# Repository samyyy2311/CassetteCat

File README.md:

# CassetteCat

<p align="center">
  <strong>A privacy-first Android music player for local media ownership and self-hosted streaming.</strong>
</p>

<p align="center">
  Desktop app: <a href="https://github.com/samyyy2311/CassetteCat-Desktop">CassetteCat Desktop</a> (Windows, macOS, Linux)
</p>

<p align="center">
  Website: <a href="https://cassettecat.caffeinelabs.in">cassettecat.caffeinelabs.in</a> · User guide: <a href="https://cassettecat.caffeinelabs.in/docs">cassettecat.caffeinelabs.in/docs</a>
</p>

<p align="center">

  <br />

</p>

---

## Install

<table align="center">
  <tr>
    <td align="center"></td>
    <td align="center"></td>
    <td align="center"></td>
    <td align="center"></td>
    <td align="center"></td>
  </tr>
</table>

<p align="center">
  <strong>Android 8.0+</strong><br />
  Download the latest APK directly from GitHub or use Obtainium for automatic update tracking. F-Droid and OpenAPK listings are pending.
</p>

---

## Screenshots

---

## Features

### Audio & Playback

- **Media3 Playback Engine**: Background audio playback with lock screen
  controls, system media notifications, and state restoration on launch.
- **Hardware Equalizer & DSP**: 5-band graphic EQ, bass boost, virtualizer, and
  loudness enhancer. Includes calibrated headphone presets powered by
  [AutoEq](https://github.com/jaakkopasanen/AutoEq).
- **Volume Normalization (ReplayGain)**: Automatic track volume balancing to
  avoid sudden loudness spikes.
- **Volume Limit (Ear Protection)**: Optional hard cap on maximum output level,
  independent of system volume.
- **Synchronized Lyrics**: Real-time karaoke-style lyrics via
  [LRCLIB](https://lrclib.net), embedded ID3 tags, and local `.lrc` sidecars
  with configurable typography scaling and keep-screen-awake mode.
- **Sleep Timer & Smart Disconnect**: Sleep timer to pause playback, plus
  instant pause when headphones or Bluetooth disconnect.

### Library & Streaming

- **Local Audio Scanning**: Scans device audio with configurable folder
  whitelists, blacklists, and short audio clip filtering.
- **A–Z Rail**: Jump through long lists with a letter badge and a light tick as
  you pass each letter.
- **Search**: Finds songs, artists, and albums as you type, matching several
  words at once.
- **Subsonic API**: Connects to Navidrome, Gonic, and Airsonic with token
  authentication.
- **Jellyfin**: Direct streaming and music library browsing from your Jellyfin
  server, with Quick Connect sign-in support.
- **Internet Radio**: Search and browse tens of thousands of live stations from
  [Radio Browser](https://www.radio-browser.info) by name, tag, or country, with
  favorites and Android Auto support.
- **Offline Cache**: Download and cache streaming tracks for offline playback.
- **Scrobbling**: Track your listening on [Last.fm](https://www.last.fm),
  [ListenBrainz](https://listenbrainz.org), and [Libre.fm](https://libre.fm).
- **Listening Record**: Your top songs, artists, and albums by month or year,
  your listening history, and a Rewind poster to share.
- **Listening Room**: Sync playback with nearby devices over your local Wi-Fi.

### Planned Companion Hardware

> The companion protocol is present in the Android app, but the `firmware/` and
> `hardware/` directories currently contain design placeholders rather than
> buildable firmware or fabrication files.

- **Wireless Pairing**: Connect to a standalone ESP32 CassetteCat player over a
  direct SoftAP hotspot or your local Wi-Fi network via mDNS. On Android 13+,
  hotspot pairing associates automatically via `WifiNetworkSpecifier`.
- **Live Telemetry**: Battery level, charging status, SD card capacity, and
  firmware version, all from the Pairing screen.

### Device Integration

- **Android Auto**: Browse your local library (Liked Songs, Playlists, Albums,
  Artists, All Songs) and radio favourites, search, and control playback from
  the car.
- **Quick Settings Tile**: Play, pause, and see what's playing without opening
  the app.
- **Desktop Remote**: Pick your computer from the devices button to control
  [CassetteCat Desktop](https://github.com/samyyy2311/CassetteCat-Desktop) on
  the same Wi-Fi, move your song, queue and position between the two, and
  browse the computer's music from your phone.

### Design & Customization

- **Curated Theme Accents**: 6 dynamic color palettes: _Record Red_, _Cassette
  Amber_, _Electric Cyan_, _Neon Emerald_, _Tape Magenta_, and _Monochrome
  Silver_.
- **Pure Black AMOLED Mode**: Pitch black `#000000` surface backgrounds for true
  OLED blacks and maximum battery efficiency.
- **Now Playing & Artwork Styling**: Configurable album art corner radii (Curved
  16dp, Soft 8dp, Vinyl Square 0dp) and interactive remaining time countdown
  toggle (`-02:45`).
- **Navigation & Startup Preferences**: Configurable default landing screen
  (_Home_, _Library_, or _Last active tab_) and default Library section.
- **Share Cards**: Share a song or a few lines of its lyrics as a 2160×2700
  image.
- **Home Screen Widget**: Resizable, with the current song and artwork, play
  controls, shuffle, repeat, and like, in your accent colour. Play works even
  after the app is closed.

### Privacy

- Local-first architecture: no analytics, no third-party tracking, zero Google
  Play Services dependencies.
- Streaming server credentials encrypted with AES-256 via the hardware-backed
  `AndroidKeyStore`.
- Fully open source under GPL-3.0.
- F-Droid submission pending.

---

## Building

```bash
cd app
./gradlew assembleDebug
./gradlew testDebugUnitTest
```

Output:

```text
app/app/build/outputs/apk/debug/app-debug.apk
```

---

## Documentation

- [User guide](https://cassettecat.caffeinelabs.in/docs): setup, every feature, and troubleshooting
- [Developer guide](docs/README.md#working-on-the-code): building, architecture, how-tos and releasing
- [Privacy Policy](PRIVACY_POLICY.md)
- [Third-Party Notices](THIRD_PARTY_NOTICES.md)

---

## Contributing

Bug reports, ideas and pull requests are welcome. Read [CONTRIBUTING.md](CONTRIBUTING.md) before opening a pull
request, and [AI_DISCLOSURE.md](AI_DISCLOSURE.md) for how AI assistance is used here.

### Translations

Translate the app in your browser on Weblate, with no coding needed. Weblate sends your work here as a pull request,
and anything not translated yet shows in English. See [TRANSLATING.md](TRANSLATING.md) for a few guidelines. The
desktop app is English only for now ([CassetteCat-Desktop#56](https://github.com/samyyy2311/CassetteCat-Desktop/issues/56)).

---

## Support

CassetteCat is free, with no ads and no tracking. If it's useful to you, you can support its development:

---

## Credits

### Services & Data

| Project | Used for |
| :--- | :--- |
| [LRCLIB](https://lrclib.net) | Synchronized and plain lyrics |
| [Cover Art Archive](https://coverartarchive.org) | Album artwork from MetaBrainz and the Internet Archive |
| [MusicBrainz](https://musicbrainz.org) | Music metadata and encyclopedia |
| [Last.fm](https://www.last.fm) | Scrobbling |
| [ListenBrainz](https://listenbrainz.org) | Open scrobbling |
| [Radio Browser](https://www.radio-browser.info) | Internet radio station directory |
| [Libre.fm](https://libre.fm) | Free software scrobbling (GNU FM) |
| [Wikipedia](https://wikipedia.org) | Artist biographies (CC BY-SA 4.0) |
| [Deezer](https://deezer.com) and [TheAudioDB](https://theaudiodb.com) | Artist imagery and metadata |
| [GitHub](https://github.com) | Release update checks |

### Libraries & Design

| Project | Used for |
| :--- | :--- |
| [AutoEq](https://github.com/jaakkopasanen/AutoEq) | Headphone EQ profiles by Jaakko Pasanen |
| [AndroidX Media3](https://developer.android.com/media/media3) | Playback engine and caching |
| [Jetpack Compose](https://developer.android.com/jetpack/compose) | UI toolkit |
| [Lucide](https://lucide.dev) | App logo and icons (ISC) |
| [Simple Icons](https://simpleicons.org) | Brand icons (CC0 1.0) |
| [OkHttp](https://github.com/square/okhttp) | HTTP client |
| [IBM Plex](https://github.com/IBM/plex) | Typefaces (OFL 1.1) |
| [Space Grotesk](https://github.com/floriankarsten/space-grotesk) | Display font by Florian Karsten (OFL 1.1) |

---

## Desktop

CassetteCat is also available for Windows, macOS, and Linux at
[CassetteCat-Desktop](https://github.com/samyyy2311/CassetteCat-Desktop).

---

## Acknowledgements

<p align="center">

</p>

<p align="center">
  Thanks to <a href="https://coderabbit.ai">CodeRabbit</a> for free code reviews on open-source projects like this one, to <a href="https://hosted.weblate.org/engage/cassettecat/">Weblate</a> for hosting translations, and to <a href="https://www.codacy.com">Codacy</a>, <a href="https://www.codefactor.io">CodeFactor</a> and <a href="https://www.mintlify.com">Mintlify</a> for their free plans for open source.
</p>

---

## License

CassetteCat is licensed under the
[GNU General Public License v3.0 (GPL-3.0)](LICENSE).

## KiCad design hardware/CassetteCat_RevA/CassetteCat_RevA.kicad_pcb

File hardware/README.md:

# CassetteCat Hardware

PCB schematics, board layouts, and mechanical design files for the CassetteCat player. Licensed under [CERN-OHL-S-2.0](LICENSE).

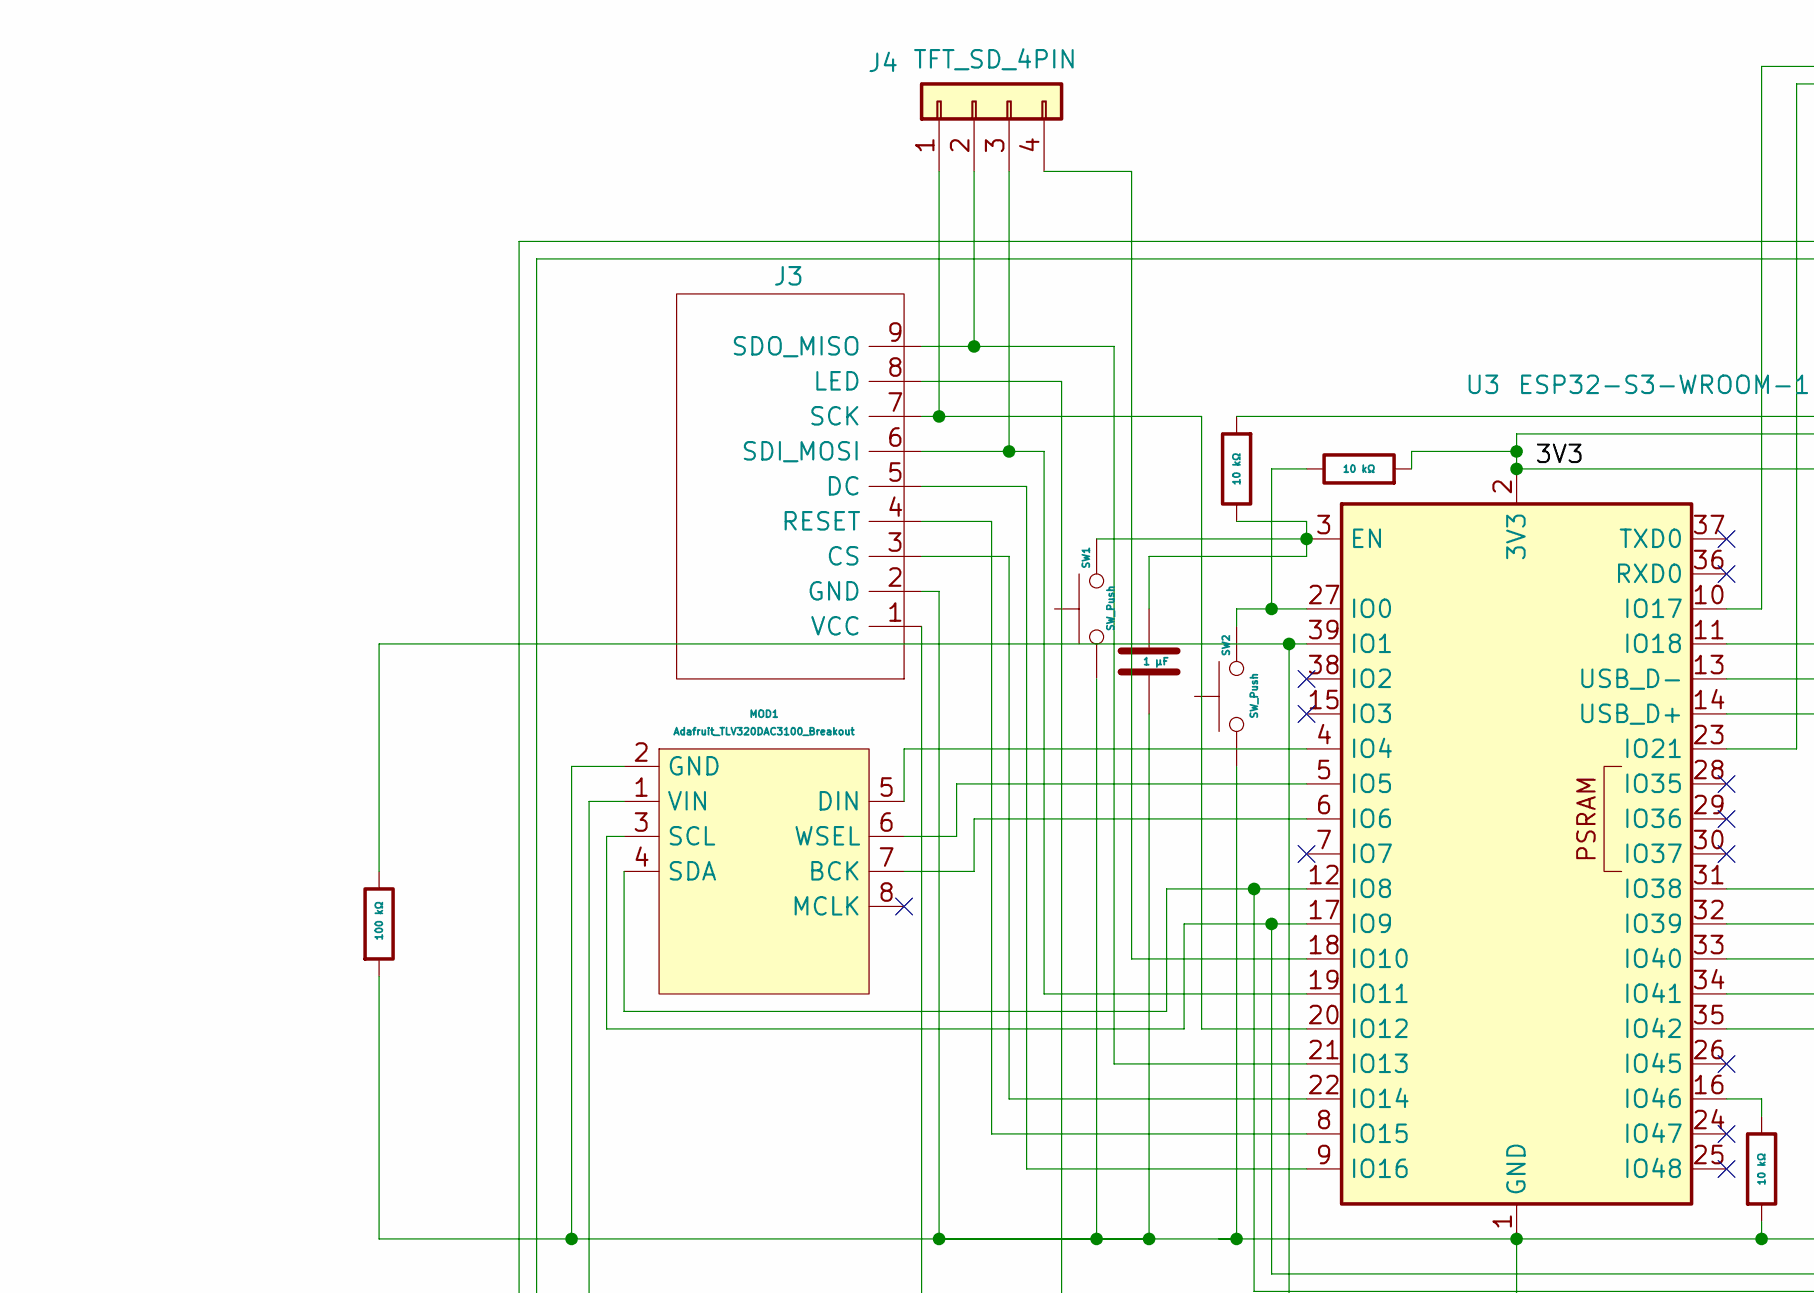
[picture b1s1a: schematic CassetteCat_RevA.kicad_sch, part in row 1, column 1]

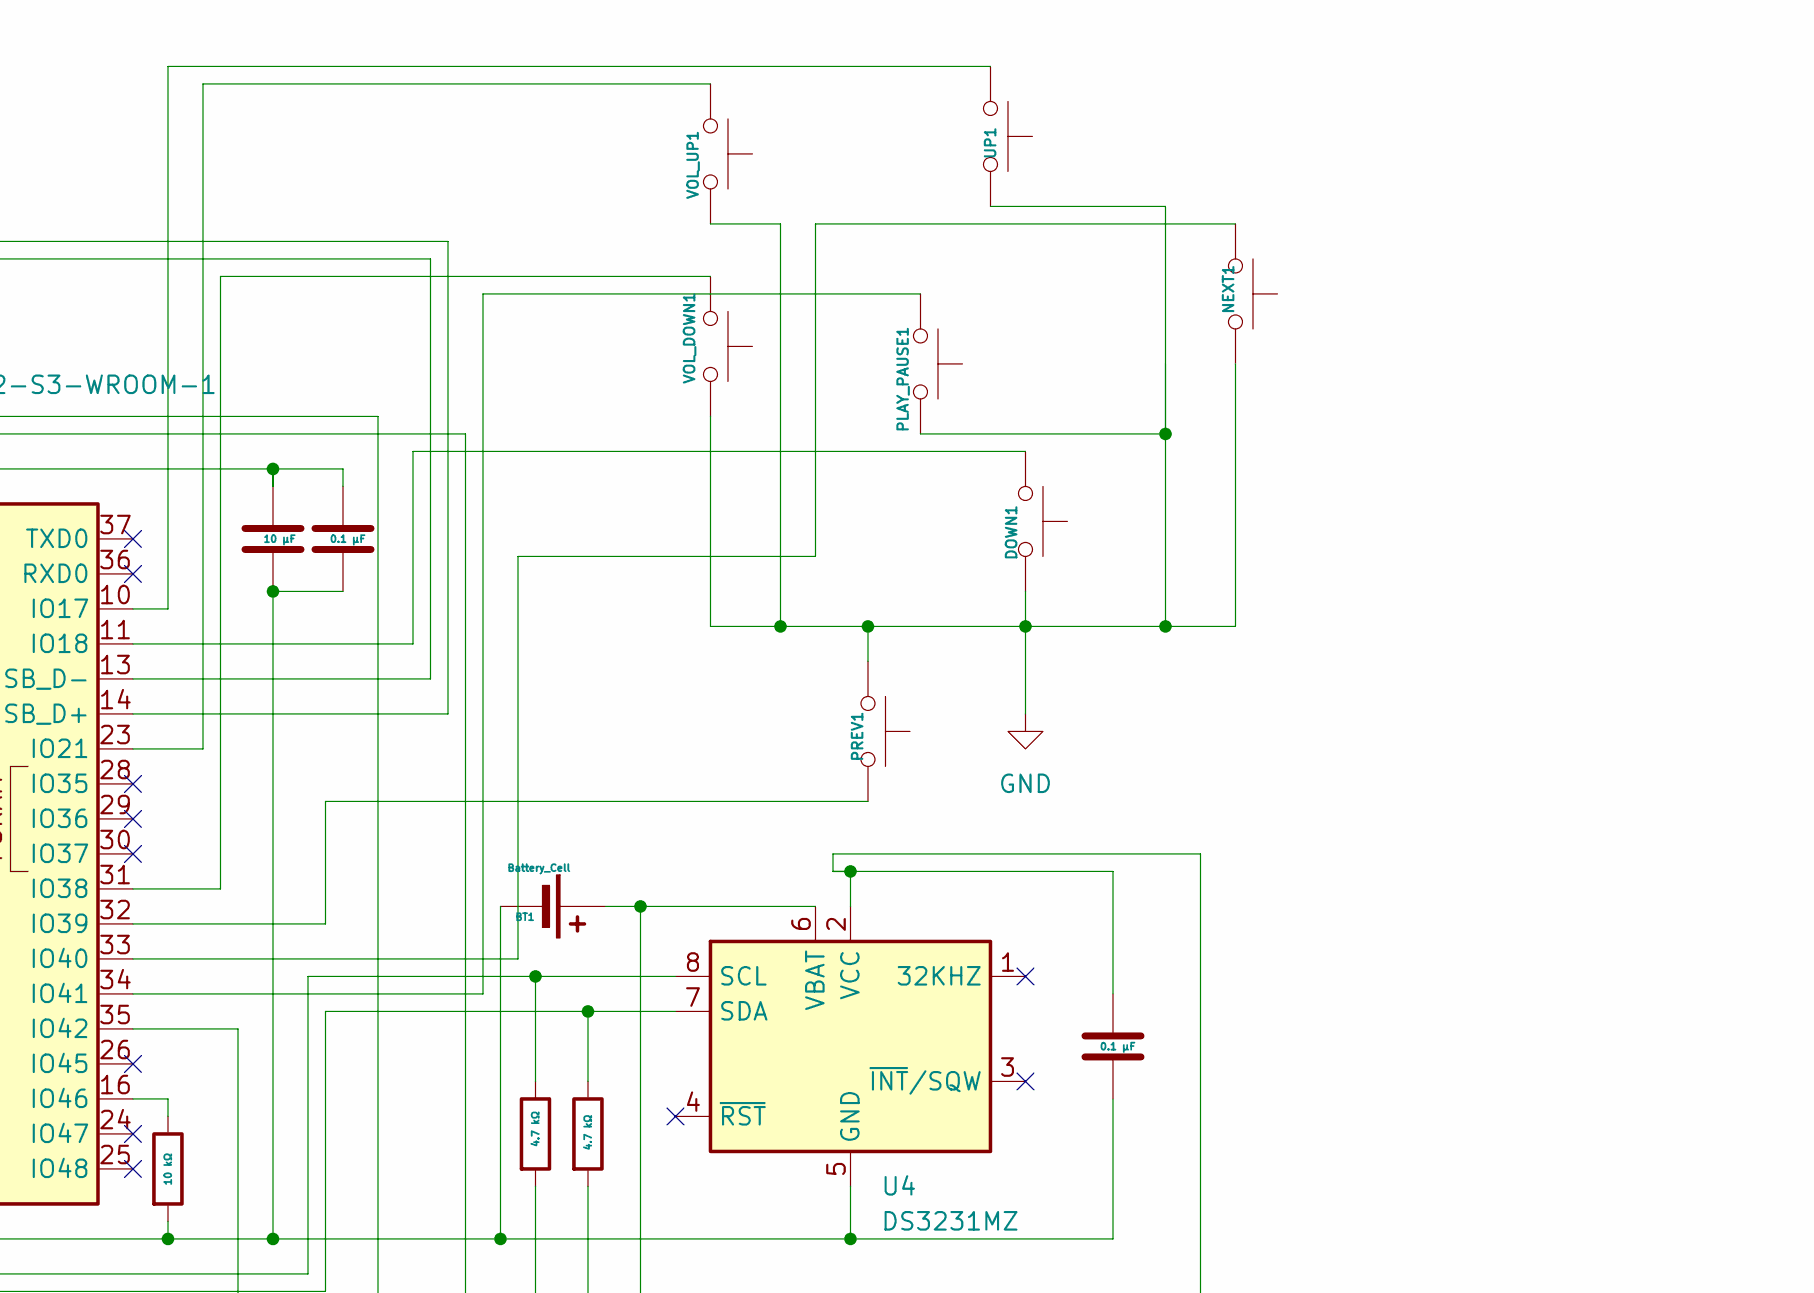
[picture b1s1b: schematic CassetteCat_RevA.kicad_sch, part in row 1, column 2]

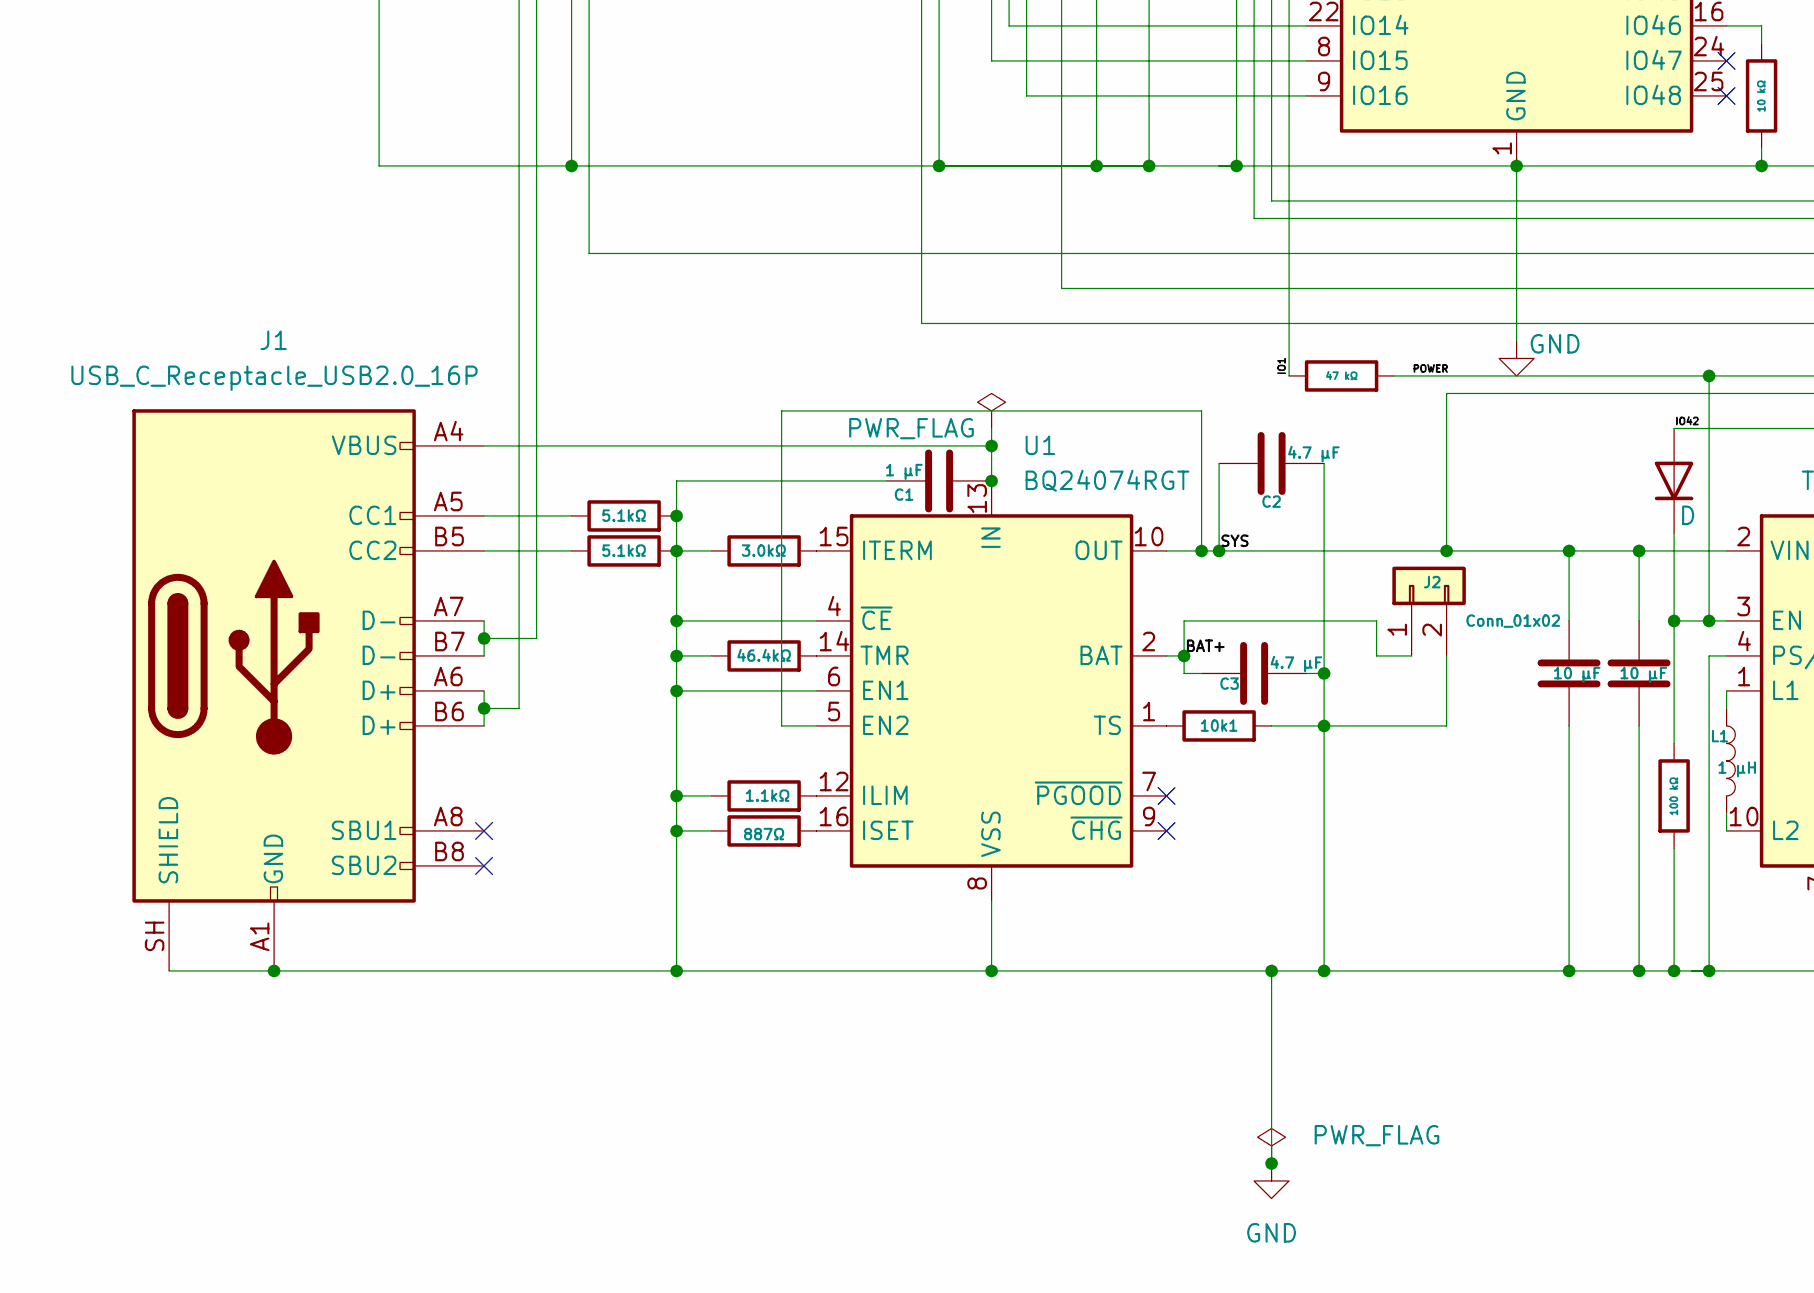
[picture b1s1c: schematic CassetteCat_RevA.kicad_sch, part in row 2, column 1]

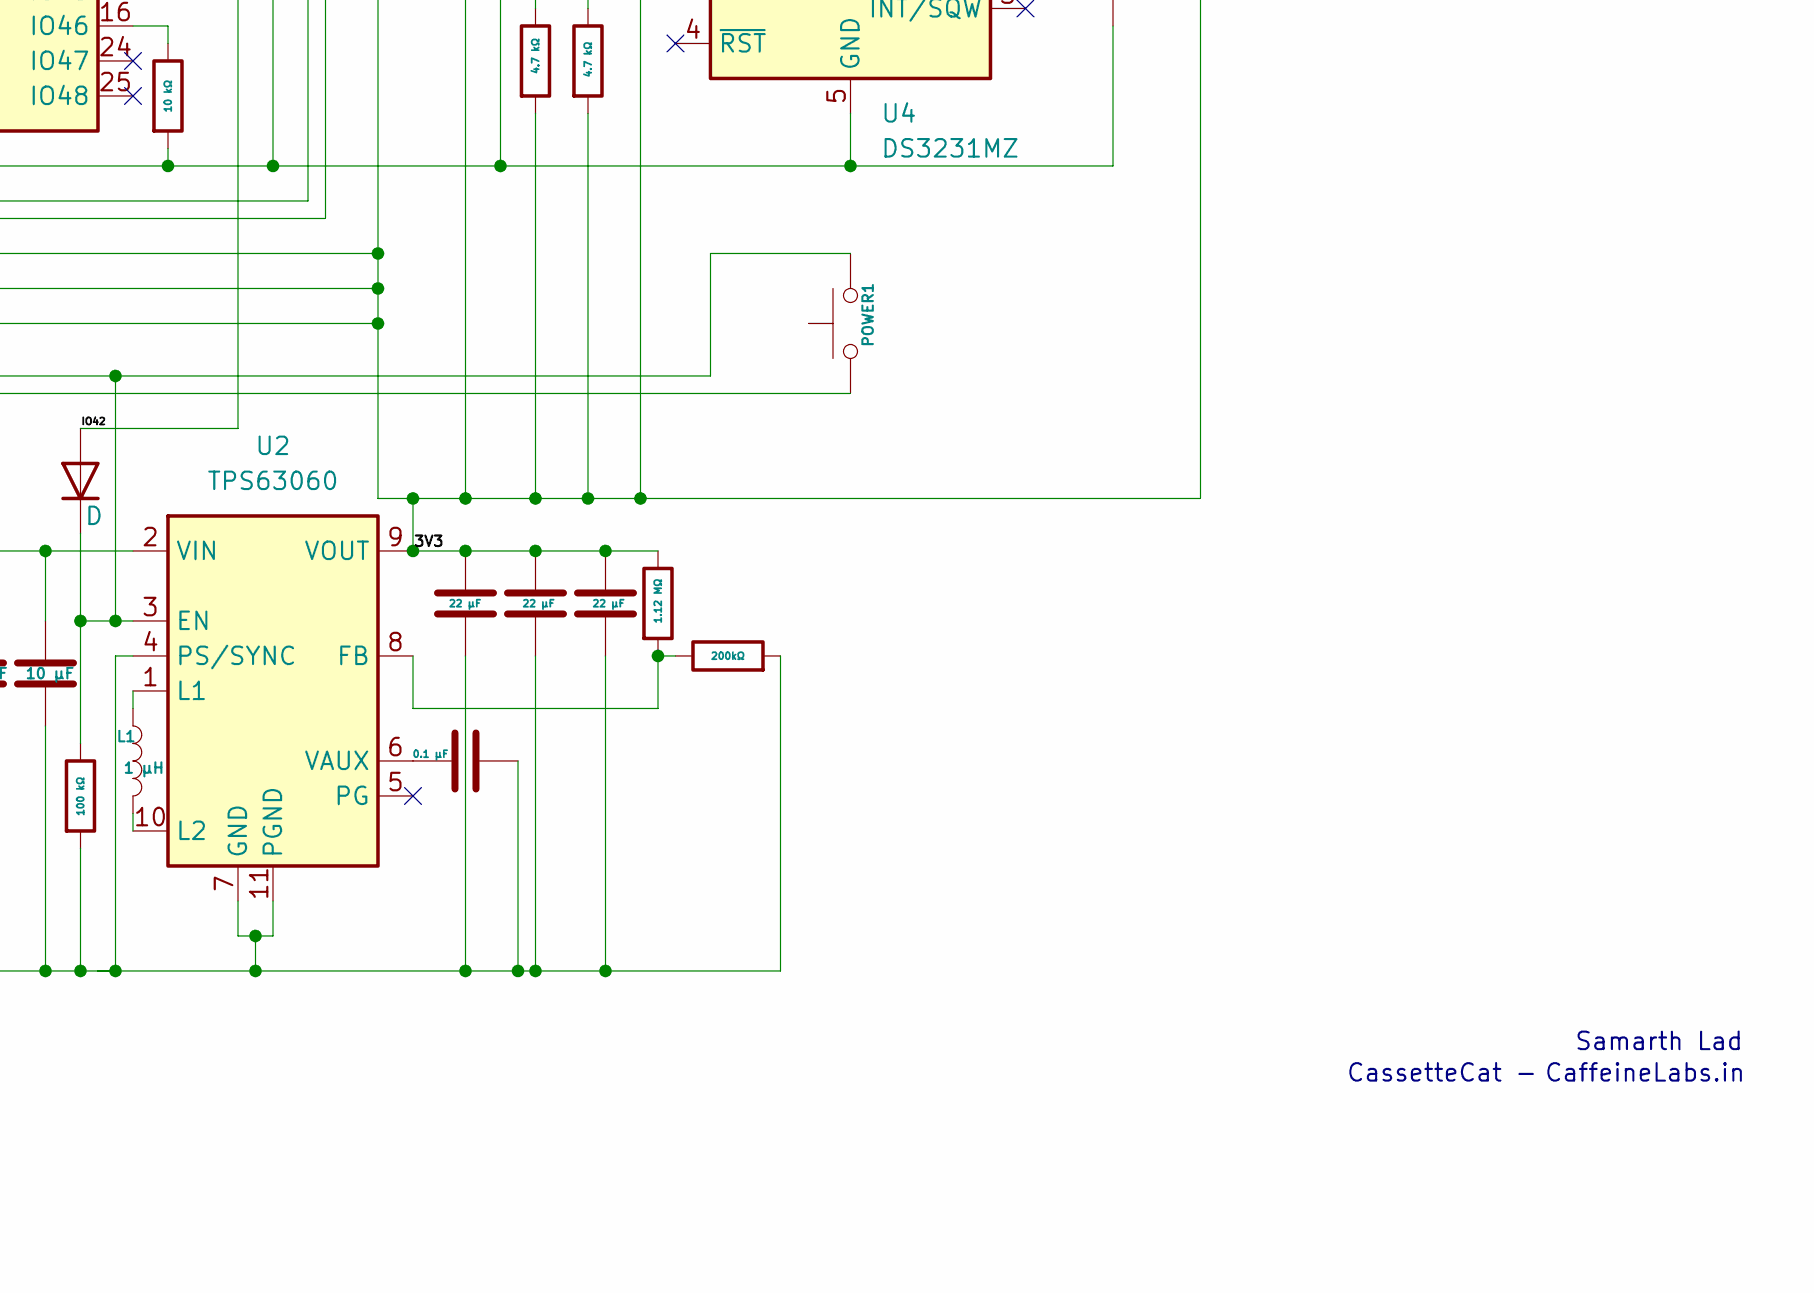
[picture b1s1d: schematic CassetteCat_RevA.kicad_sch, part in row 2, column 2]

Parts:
10k1: R; R_0603_1608Metric
BT1: Battery_Cell; BatteryHolder_LINX_BAT-HLD-012-SMT
C1, C9: 1 µF; C_0603_1608Metric
C2, C3: 4.7 µF; C_0805_2012Metric
C4, C5, C10: 10 µF; C_0805_2012Metric
C6, C7, C13: 22 µF; C_1206_3216Metric
C8, C11, C12: 0.1 µF; C_0603_1608Metric
D1: D; D_SOD-123
DOWN1: SW_Push; SW_SPST_B3S-1000
J1: USB_C_Receptacle_USB2.0_16P; USB_C_Receptacle_HRO_TYPE-C-31-M-12
J2: Conn_01x02; JST_PH_B2B-PH-K_1x02_P2.00mm_Vertical
J3: PinHeader_1x09_P2.54mm_Vertical
J4: TFT_SD_4PIN; PinHeader_1x04_P2.54mm_Vertical
L1: 1 µH; L_Sunlord_SWPA8040S
MOD1: Adafruit_TLV320DAC3100_Breakout; PinHeader_1x08_P2.54mm_Vertical
NEXT1: SW_Push; SW_SPST_B3S-1000
PLAY_PAUSE1: SW_Push; SW_SPST_B3S-1000
POWER1: SW_Push; SW_SPST_B3S-1000
PREV1: SW_Push; SW_SPST_B3S-1000
R1, R2: 5.1kΩ; R_0603_1608Metric
R3: 1.1kΩ; R_0603_1608Metric
R4: 887Ω; R_0603_1608Metric
R5: 3.0kΩ; R_0603_1608Metric
R6: 46.4kΩ; R_0603_1608Metric
R7: 200kΩ; R_0603_1608Metric
R8: 1.12 MΩ; R_0603_1608Metric
R9, R10, R11: 10 kΩ; R_0603_1608Metric
R12, R13: 4.7 kΩ; R_0603_1608Metric
R14, R16: 100 kΩ; R_0603_1608Metric
R15: 47 kΩ; R_0603_1608Metric
SW1, SW2: SW_Push; SW_SPST_B3S-1000
U1: BQ24074RGT; VQFN-16-1EP_3x3mm_P0.5mm_EP1.6x1.6mm
U2: TPS63060; Texas_S-PWSON-N10_ThermalVias
U3: ESP32-S3-WROOM-1
U4: DS3231MZ; SOIC-8_3.9x4.9mm_P1.27mm
UP1: SW_Push; SW_SPST_B3S-1000
VOL_DOWN1: SW_Push; SW_SPST_B3S-1000
VOL_UP1: SW_Push; SW_SPST_B3S-1000

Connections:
/3V3: BT1.1 (+), C6.1, C7.1, C10.1, C11.1, C12.1, C13.1, J3.1 (VCC), J3.8 (LED), MOD1.1 (VIN), R8.1, R9.2, R10.2, R12.2, R13.2, U2.9 (VOUT), U3.2 (3V3), U4.2 (VCC), U4.6 (VBAT)
/BAT+: C3.1, J2.1, U1.2 (BAT), U1.3 (BAT)
/IO1: R15.1, R16.1, U3.39 (IO1)
/IO42: D1.2 (A), U3.35 (IO42)
/POWER: D1.1 (K), POWER1.2, R14.1, R15.2, U2.3 (EN)
/SYS: C2.1, C4.1, C5.1, POWER1.1, U1.5 (EN2), U1.10 (OUT), U1.11 (OUT), U2.2 (VIN)
GND: 10k1.2, BT1.2 (-), C1.1, C2.2, C3.2, C4.2, C5.2, C6.2, C7.2, C8.2, C9.2, C10.2, C11.2, C12.2, C13.2, DOWN1.2, J1.A1 (GND), J1.A12 (GND), J1.B1 (GND), J1.B12 (GND), J1.SH (SHIELD), J2.2, J3.2 (GND), MOD1.2 (GND), NEXT1.2, PLAY_PAUSE1.2, PREV1.1, R1.2, R2.2, R3.1, R4.1, R5.1, R6.1, R7.2, R11.2, R14.2, R16.2, SW1.1, SW2.1, U1.4 (~CE), U1.6 (EN1), U1.8 (VSS), U1.17 (VSS), U2.4 (PS/SYNC), U2.7 (GND), U2.11 (PGND), U3.1 (GND), U3.40 (GND), U3.41 (GND), U4.5 (GND), UP1.2, VOL_DOWN1.2, VOL_UP1.2
unnamed: J1.A5 (CC1), R1.1
unnamed: J1.B5 (CC2), R2.1
unnamed: J3.3 (CS), U3.22 (IO14)
unnamed: J3.5 (DC), U3.9 (IO16)
unnamed: J3.4 (RESET), U3.8 (IO15)
unnamed: J3.7 (SCK), J4.1 (SD_SCK), U3.20 (IO12)
unnamed: J3.6 (SDI_MOSI), J4.3 (SD_MOSI), U3.19 (IO11)
unnamed: J3.9 (SDO_MISO), J4.2 (SD_MISO), U3.21 (IO13)
unnamed: J4.4 (SD_CS), U3.18 (IO10)
unnamed: MOD1.7 (BCK), U3.6 (IO6)
unnamed: MOD1.5 (DIN), U3.4 (IO4)
unnamed: MOD1.3 (SCL), R13.1, U3.17 (IO9), U4.8 (SCL)
unnamed: MOD1.4 (SDA), R12.1, U3.12 (IO8), U4.7 (SDA)
unnamed: MOD1.6 (WSEL), U3.5 (IO5)
unnamed: R3.2, U1.12 (ILIM)
unnamed: C1.2, J1.A4 (VBUS), J1.A9 (VBUS), J1.B4 (VBUS), J1.B9 (VBUS), U1.13 (IN)
unnamed: R4.2, U1.16 (ISET)
unnamed: R5.2, U1.15 (ITERM)
unnamed: R6.2, U1.14 (TMR)
unnamed: 10k1.1, U1.1 (TS)
unnamed: R7.1, R8.2, U2.8 (FB)
unnamed: L1.1, U2.1 (L1)
unnamed: L1.2, U2.10 (L2)
unnamed: C8.1, U2.6 (VAUX)
unnamed: C9.1, R9.1, SW1.2, U3.3 (EN)
unnamed: R10.1, SW2.2, U3.27 (IO0)
unnamed: U3.10 (IO17), UP1.1
unnamed: DOWN1.1, U3.11 (IO18)
unnamed: U3.23 (IO21), VOL_UP1.1
unnamed: U3.31 (IO38), VOL_DOWN1.1
unnamed: PREV1.2, U3.32 (IO39)
unnamed: NEXT1.1, U3.33 (IO40)
unnamed: PLAY_PAUSE1.1, U3.34 (IO41)
unnamed: R11.1, U3.16 (IO46)
unnamed: J1.A6 (D+), J1.B6 (D+), U3.14 (USB_D+)
unnamed: J1.A7 (D-), J1.B7 (D-), U3.13 (USB_D-)

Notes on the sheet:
Samarth Lad
CaffeineLabs.in
CassetteCat -

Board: 2 copper layers, 52 parts (1 on the bottom side), 43 nets, no tracks yet.
